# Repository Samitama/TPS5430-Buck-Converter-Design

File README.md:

# TPS5430
 Buck Converter

3D View

Schematic Design

PCB Design

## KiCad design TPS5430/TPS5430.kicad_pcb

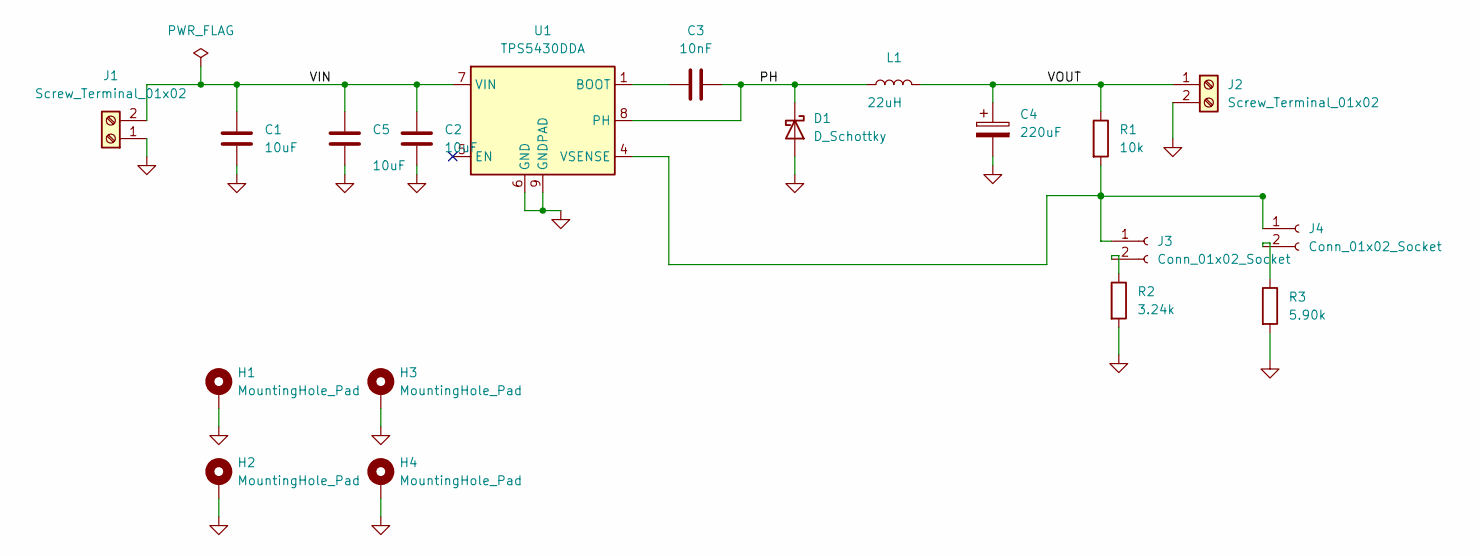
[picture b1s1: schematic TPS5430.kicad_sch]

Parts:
C1, C2, C5: 10uF; C_1210_3225Metric_Pad1.33x2.70mm_HandSolder
C3: 10nF; C_0805_2012Metric_Pad1.18x1.45mm_HandSolder
C4: 220uF; CP_Elec_6.3x5.9
D1: D_Schottky; D_SMC_Handsoldering
H1, H2, H3, H4: MountingHole_Pad; MountingHole_3.2mm_M3_Pad_Via
J1, J2: Screw_Terminal_01x02; TerminalBlock_Phoenix_MKDS-1,5-2-5.08_1x02_P5.08mm_Horizont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
J3, J4: Conn_01x02_Socket; PinHeader_1x02_P2.54mm_Vertical
L1: 22uH; L_Wuerth_WE-PD-Typ-LS_Handsoldering
R1: 10k; R_0805_2012Metric_Pad1.20x1.40mm_HandSolder
R2: 3.24k; R_0805_2012Metric_Pad1.20x1.40mm_HandSolder
R3: 5.90k; R_0805_2012Metric_Pad1.20x1.40mm_HandSolder
U1: TPS5430DDA; TI_SO-PowerPAD-8_ThermalVias

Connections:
/PH: C3.2, D1.1 (K), L1.1, U1.8 (PH)
/VIN: C1.1, C2.1, C5.1, J1.2, U1.7 (VIN)
/VOUT: C4.1, J2.1, L1.2, R1.1
GND: C1.2, C2.2, C4.2, C5.2, D1.2 (A), H1.1, H2.1, H3.1, H4.1, J1.1, J2.2, R2.2, R3.2, U1.6 (GND), U1.9 (GNDPAD)
unnamed: J3.1, J4.1, R1.2, U1.4 (VSENSE)
unnamed: J3.2, R2.1
unnamed: J4.2, R3.1
unnamed: C3.1, U1.1 (BOOT)

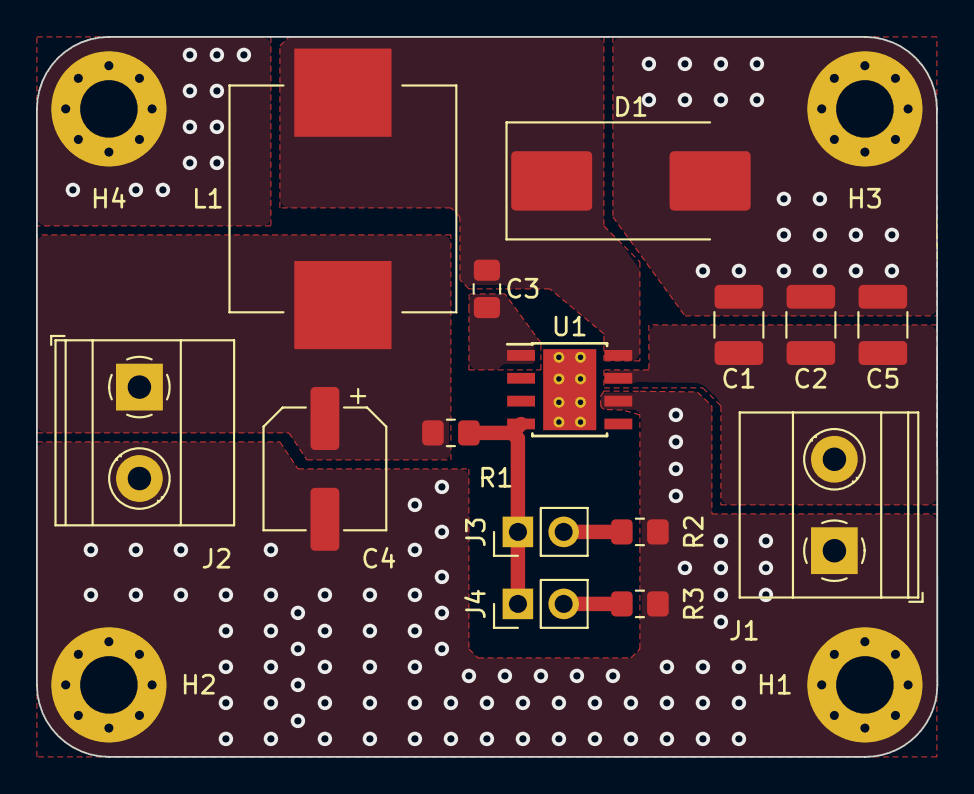
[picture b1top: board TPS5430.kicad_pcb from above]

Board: 2 copper layers, 50.0 x 40.0 mm, 19 parts (0 on the bottom side), 8 nets.

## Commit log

2024-11-13 Buck Converter Design
    My Buck Converter Design
